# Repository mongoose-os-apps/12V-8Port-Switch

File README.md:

# ESP8266 based 12V switch

This is a project that uses an ESP8266 to drive 8x MOSFET power ports, rated at 2A each. It incorporates a GPIO buffer (based on [MCP23008](docs/mcp23008.pdf)) to allow the MCU to reboot without changing the port status, and a current sensor (based on [INA219](docs/ina219.pdf)) to measure total current through the device.

## Hardware

The schematic and board layout are in the [eagle/](eagle/) directory. You can order this board from [Oshpark](https://oshpark.com/shared_projects/42dmo9fg).

Logical components in the hardware are:

*   An LDO that steps down 12V input to 3.3V, with power LED
*   An INA219 on I2C that senses current using a 0.01 Ohm shunt resistor (32A max in 80mA steps)
*   An MCP23008 8-port GPIO expander on I2C
*   8 output ports, driven by IRLML6244 mosfets (3A max per channel)
*   An ESP8266-12E which drives the current sensor and GPIO expander over I2C
    *    RST and GPIO0 are provided via pushbuttons
*   Headers:
    *    I2C breakout for additional sensor(s)
    *    4x GPIO breakouts (GPIO: 4, 5, 9, 10)
    *    Serial access to flash the ESP8266

### BOM

Bill of materials with components and sizes:

*   AM1117-3.3V
*   C1, C2: 10uF Tantalum (3216)
*   C3: 470pF ceramic (0805)
*   IC1: MCP23008 (SO18W)
*   IO0/RST: momentary switch (6mm x 3.5mm)
*   J1-J9: screw terminal (0.2" pitch)
*   J10,J11: 4-pin standard header (0.1" pitch)
*   J12-15: 3-pin standard header (0.1" pitch)
*   MDL1: ESP8266-ESP12E
*   PWR: Green LED (0805)
*   Q1-Q8: IRLML6244 (SOT23)
*   R1-R8: 1kOhm (0805)
*   R9-R10, R12-16: 10kOhm (0805)
*   R11: 330Ohm (0805)
*   R17: 0.01Ohm Shunt (2515)
*   U1: INA219 (SOT23-8)

## Software

We use drivers for [INA219](https://github.com/mongoose-os-libs/ina219-i2c/) and [MCP23008](https://github.com/mongoose-os-libs/mcp23xxx) which are readily available for Mongoose OS. For telemetry export, we use [Prometheus](https://github.com/mongoose-os-libs/prometheus-metrics) to export metrics including standard telemetry from the ESP8266 as well as custom metrics such as port state, current and voltage.

Using the Mongoose OS [RPC Subsystem](https://github.com/mongoose-os-libs/rpc-common), we expose a simple control surface to query the ports, switch them on/off or toggle them.

By default, HTTP endpoints are provided for metrics and RPCs, which can be a security hazard. For non-trusted wifi environments, we allow allow the device to close all serving ports and service RPCs via [Pubsub](https://github.com/mongoose-os-libs/mqtt) using TLS connections to a remote [Mosquitto](https://mosquitto.org/) endpoint. Metrics can be pushed via POST requests to a Prometheus [pushgateway](https://github.com/prometheus/pushgateway).

Firmware updates can be performed [over-the-air](https://github.com/mongoose-os-libs/ota-http-client), using both HTTP as well as MQTT transport.

### API

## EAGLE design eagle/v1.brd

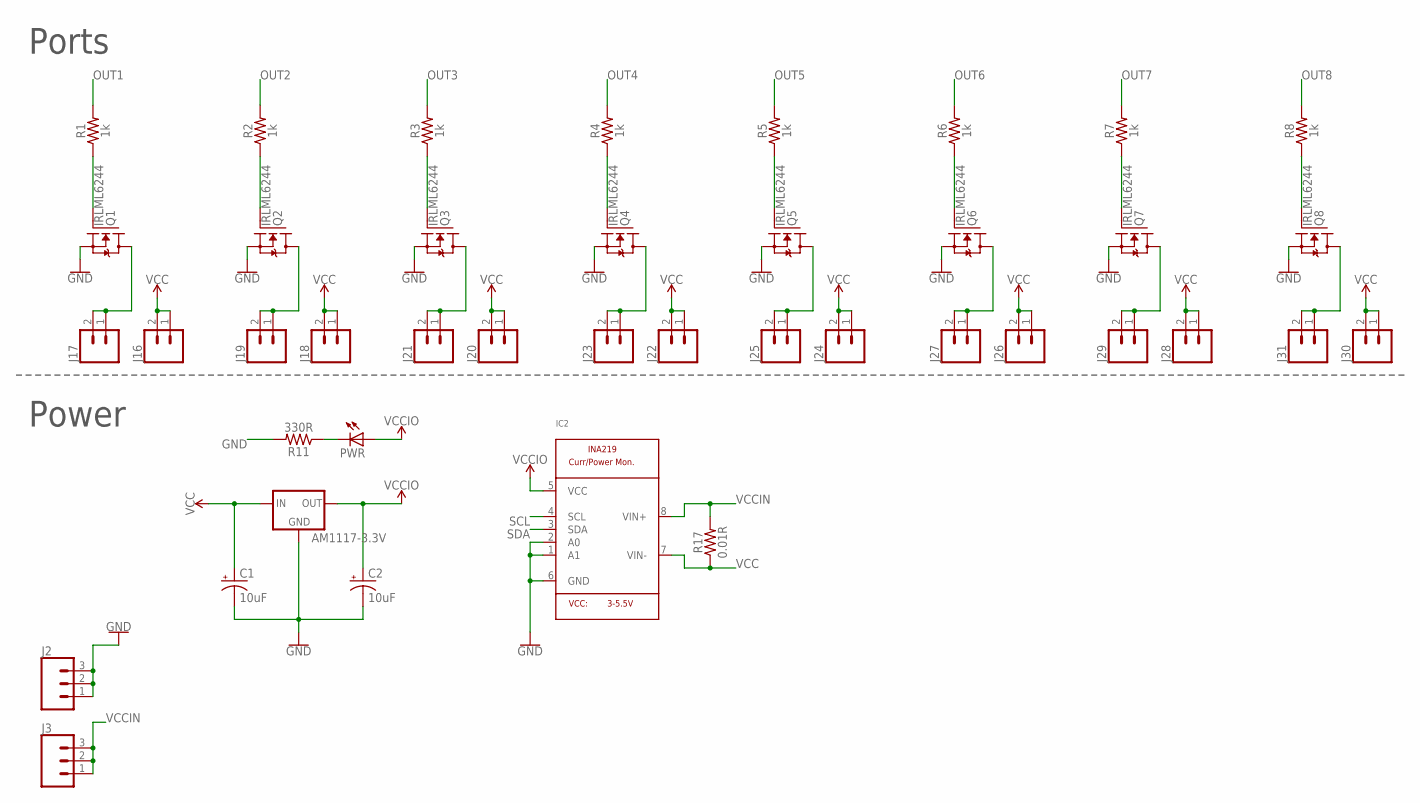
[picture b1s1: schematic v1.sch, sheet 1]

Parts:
AM1117-3.3V: V_REG_LD1117VXXLD1117-SMD; SOT223
C1, C2: 10uF; EIA3216
IC2: INA219SOIC8; SO08
J2, J3: CONN_03LONGPADS; 1X03_LONGPADS
J16, J17, J18, J19, J20, J21, J22, J23, J24, J25, J26, J27, J28, J29, J30, J31: CONN_02; 1X02
PWR: LEDCHIP-LED0805; CHIP-LED0805
Q1, Q2, Q3, Q4, Q5, Q6, Q7, Q8: IRLML6244; SOT23
R1, R2, R3, R4, R5, R6, R7, R8: 1k; 0805
R11: 330R; 0805
R17: 0.01R; 2512

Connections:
GND: AM1117-3.3V.1 (GND), C1.C (-), C2.C (-), IC2.1 (A1), IC2.2 (A0), IC2.6 (GND), J2.1, J2.2, J2.3, Q1.2 (S), Q2.2 (S), Q3.2 (S), Q4.2 (S), Q5.2 (S), Q6.2 (S), Q7.2 (S), Q8.2 (S), R11.2; also elsewhere on the board
unnamed: J23.1, J23.2, Q4.3 (D)
unnamed: J25.1, J25.2, Q5.3 (D)
unnamed: J27.1, J27.2, Q6.3 (D)
unnamed: Q1.1 (G), R1.1
unnamed: Q2.1 (G), R2.1
unnamed: Q3.1 (G), R3.1
unnamed: Q4.1 (G), R4.1
unnamed: Q5.1 (G), R5.1
unnamed: Q6.1 (G), R6.1
unnamed: Q7.1 (G), R7.1
unnamed: Q8.1 (G), R8.1
unnamed: PWR.C, R11.1
unnamed: J17.1, J17.2, Q1.3 (D)
unnamed: J19.1, J19.2, Q2.3 (D)
unnamed: J21.1, J21.2, Q3.3 (D)
unnamed: J29.1, J29.2, Q7.3 (D)
unnamed: J31.1, J31.2, Q8.3 (D)
OUT1: R1.2; also elsewhere on the board
OUT2: R2.2; also elsewhere on the board
OUT3: R3.2; also elsewhere on the board
OUT4: R4.2; also elsewhere on the board
OUT5: R5.2; also elsewhere on the board
OUT6: R6.2; also elsewhere on the board
OUT7: R7.2; also elsewhere on the board
OUT8: R8.2; also elsewhere on the board
SCL: IC2.4 (SCL); also elsewhere on the board
SDA: IC2.3 (SDA); also elsewhere on the board
VCC: AM1117-3.3V.3 (IN), C1.A (+), IC2.7 (VIN-), J16.1, J16.2, J18.1, J18.2, J20.1, J20.2, J22.1, J22.2, J24.1, J24.2, J26.1, J26.2, J28.1, J28.2, J30.1, J30.2, R17.P$1 (1)
VCCIN: IC2.8 (VIN+), J3.1, J3.2, J3.3, R17.P$2 (2)
VCCIO: AM1117-3.3V.2 (OUT), C2.A (+), IC2.5 (VCC), PWR.A; also elsewhere on the board

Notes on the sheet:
Power
Ports

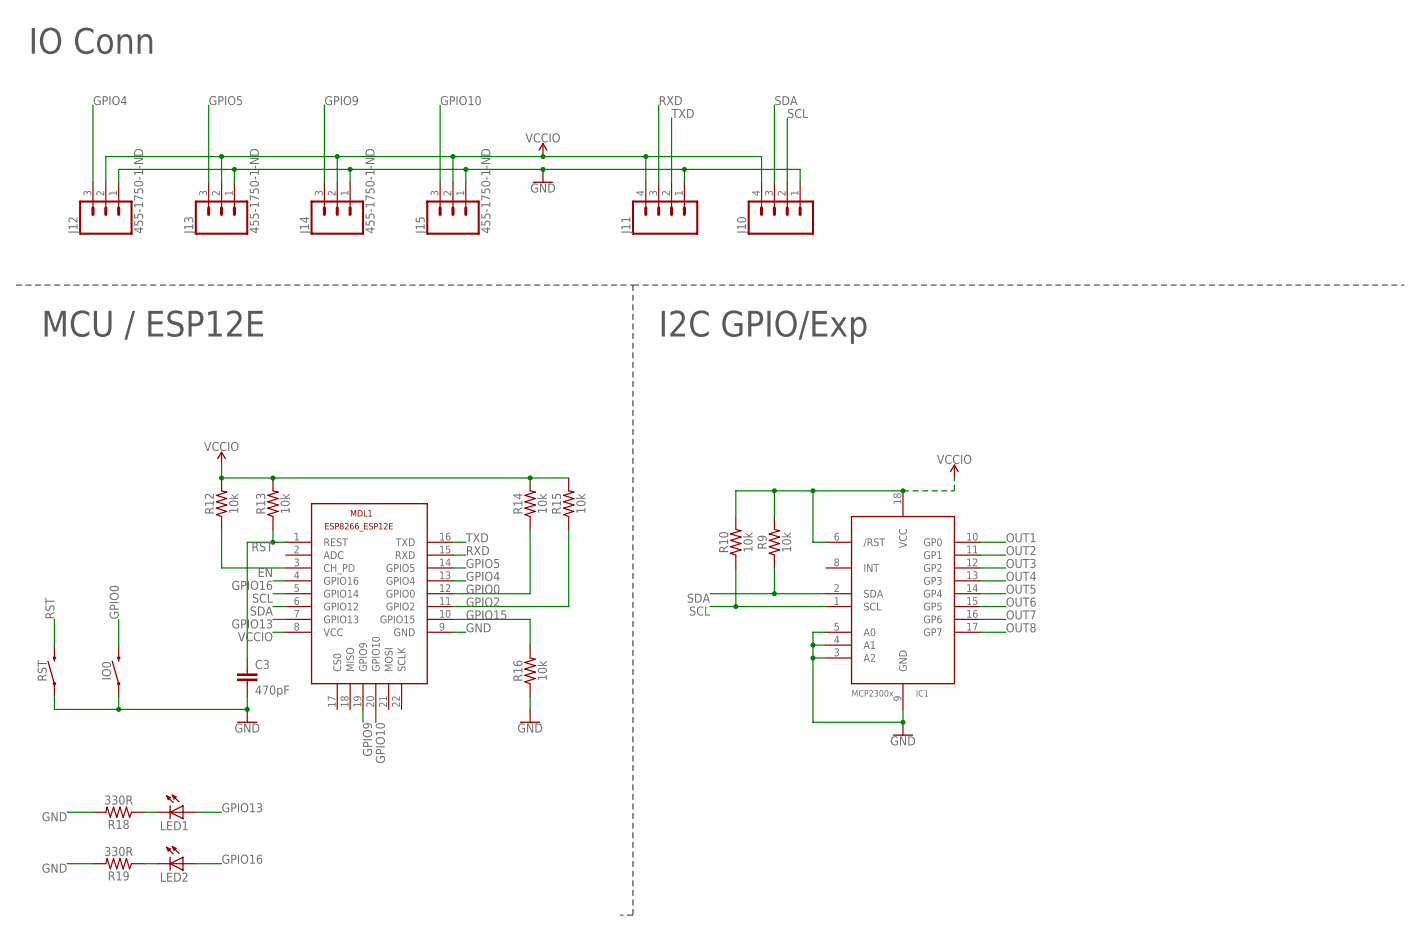
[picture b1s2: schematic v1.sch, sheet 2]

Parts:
C3: 470pF; 0805
IC1: MCP23008/SO; SO18W
IO0: MOMENTARY-SWITCH-SPST-SMD-6.0X3.5MM; TACTILE_SWITCH_SMD_6.0X3.5MM
J10, J11: CONN_04PTH; 1X04
J12, J13, J14, J15: 455-1750-1-ND; 1X03
LED1, LED2: LEDCHIP-LED0805; CHIP-LED0805
MDL1: ESP8266-12EESP8266-ESP12E; ESP8266-ESP12E
R9, R10, R12, R13, R14, R15, R16: 10k; 0805
R18, R19: 330R; 0805
RST: MOMENTARY-SWITCH-SPST-SMD-6.0X3.5MM; TACTILE_SWITCH_SMD_6.0X3.5MM

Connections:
EN: MDL1.3 (CH_PD), R12.1
GND: C3.2, IC1.3 (A2), IC1.4 (A1), IC1.5 (A0), IC1.9 (GND), IO0.1, J10.1, J11.1, J12.1, J13.1, J14.1, J15.1, MDL1.9 (GND), R16.1, R18.2, R19.2, RST.1; also elsewhere on the board
GPIO0: IO0.2, MDL1.12 (GPIO0), R14.1
GPIO2: MDL1.11 (GPIO2), R15.1
GPIO4: J12.3, MDL1.13 (GPIO4)
GPIO5: J13.3, MDL1.14 (GPIO5)
GPIO9: J14.3, MDL1.19 (GPIO9)
GPIO10: J15.3, MDL1.20 (GPIO10)
GPIO13: LED1.A, MDL1.7 (GPIO13)
GPIO15: MDL1.10 (GPIO15), R16.2
GPIO16: LED2.A, MDL1.4 (GPIO16)
unnamed: LED1.C, R18.1
unnamed: LED2.C, R19.1
OUT1: IC1.10 (GP0); also elsewhere on the board
OUT2: IC1.11 (GP1); also elsewhere on the board
OUT3: IC1.12 (GP2); also elsewhere on the board
OUT4: IC1.13 (GP3); also elsewhere on the board
OUT5: IC1.14 (GP4); also elsewhere on the board
OUT6: IC1.15 (GP5); also elsewhere on the board
OUT7: IC1.16 (GP6); also elsewhere on the board
OUT8: IC1.17 (GP7); also elsewhere on the board
RST: C3.1, MDL1.1 (REST), R13.1, RST.2
RXD: J11.3, MDL1.15 (RXD)
SCL: IC1.1 (SCL), J10.2, MDL1.5 (GPIO14), R10.1; also elsewhere on the board
SDA: IC1.2 (SDA), J10.3, MDL1.6 (GPIO12), R9.1; also elsewhere on the board
TXD: J11.2, MDL1.16 (TXD)
VCCIO: IC1.6 (/RST), IC1.18 (VCC), J10.4, J11.4, J12.2, J13.2, J14.2, J15.2, MDL1.8 (VCC), R9.2, R10.2, R12.2, R13.2, R14.2, R15.2; also elsewhere on the board

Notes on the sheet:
I2C GPIO/Exp
IO Conn
MCU / ESP12E

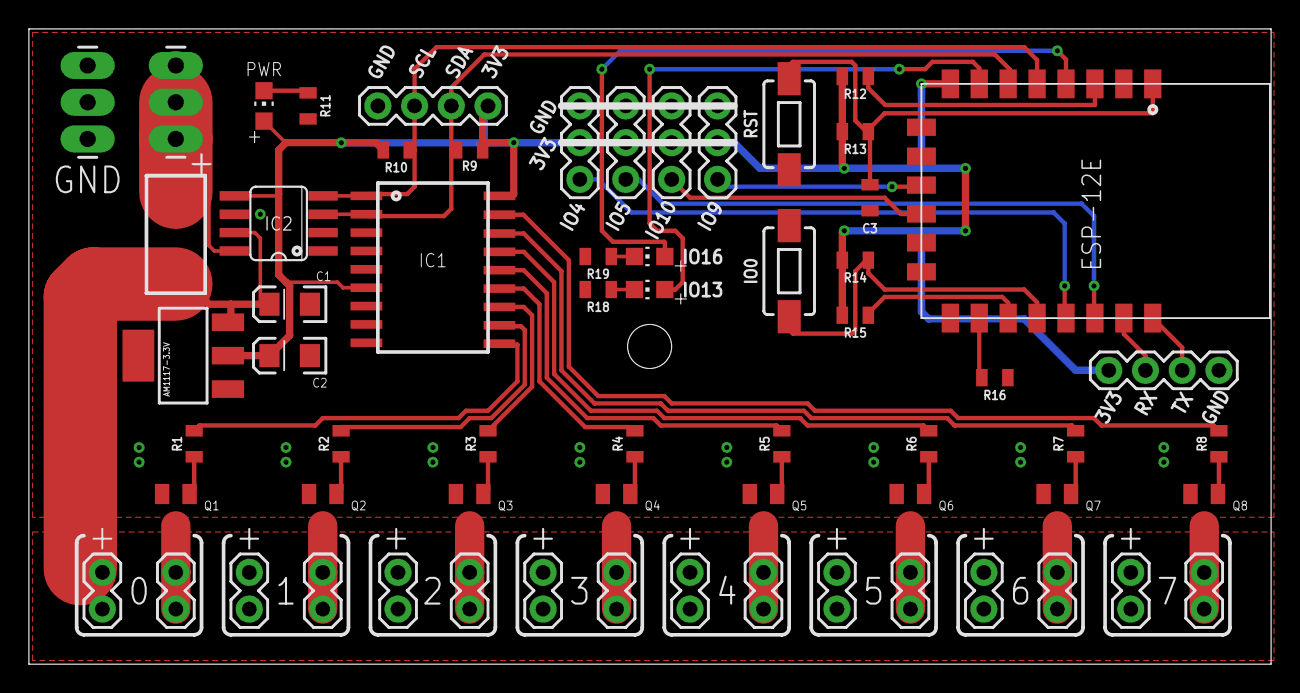
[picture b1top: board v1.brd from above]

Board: 2 copper layers, 85.9 x 43.9 mm, 63 parts (0 on the bottom side), 46 nets.

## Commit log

2019-06-04 Add Eagle schematic
2019-06-04 Empty skeleton for application
2019-06-05 Initial readme
2019-06-05 Add BOM
2019-06-05 Add oshpark link
2019-06-05 Add some software/firmware attributes
2019-06-05 Add MQTT and RPC filesystem
2019-06-05 Add OTA
2019-06-05 Fix LED polarity - caught by my dad :)
2019-06-22 Trivial example application
    - RPC interfaces:
    Channel.Get
    Channel.Set
    Channel.Toggle
    - Channel library exposing MCP23008 behind a Channel API:
    channel_get() channel_set() channel_toggle()
2019-06-22 Add a 5s timer to print channel state to serial
2019-06-28 v1 of the board -- added 2 LEDs (GPIO13, GPIO16), and swapped out INA219 from SOT23-8 to SOIC-8, and swapped out screw terminals for tabs
2019-07-09 Add INA219 current sensor, write to serial every second, add prometheus metrics exports

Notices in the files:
parts and their libraries:
SparkFun-Retired: Licensing: Creative Commons ShareAlike 4.0 International - https://creativecommons.org/licenses/by-sa/4.0
